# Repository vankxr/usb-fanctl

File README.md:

# USB Fan Controller
There are many USB fan controllers on sale, but none of them allow you to PWM 2-pin fans, as far as I am aware. This controller implements a compatible and widely supported USB serial port interface and allows you to control fans with it. It also supports 1-Wire sensors for temperature measurement.

## Authors

* **João Silva** - [vankxr](https://github.com/vankxr)

## License

The content of this repository is licensed under the [GNU General Public License v3.0](LICENSE).

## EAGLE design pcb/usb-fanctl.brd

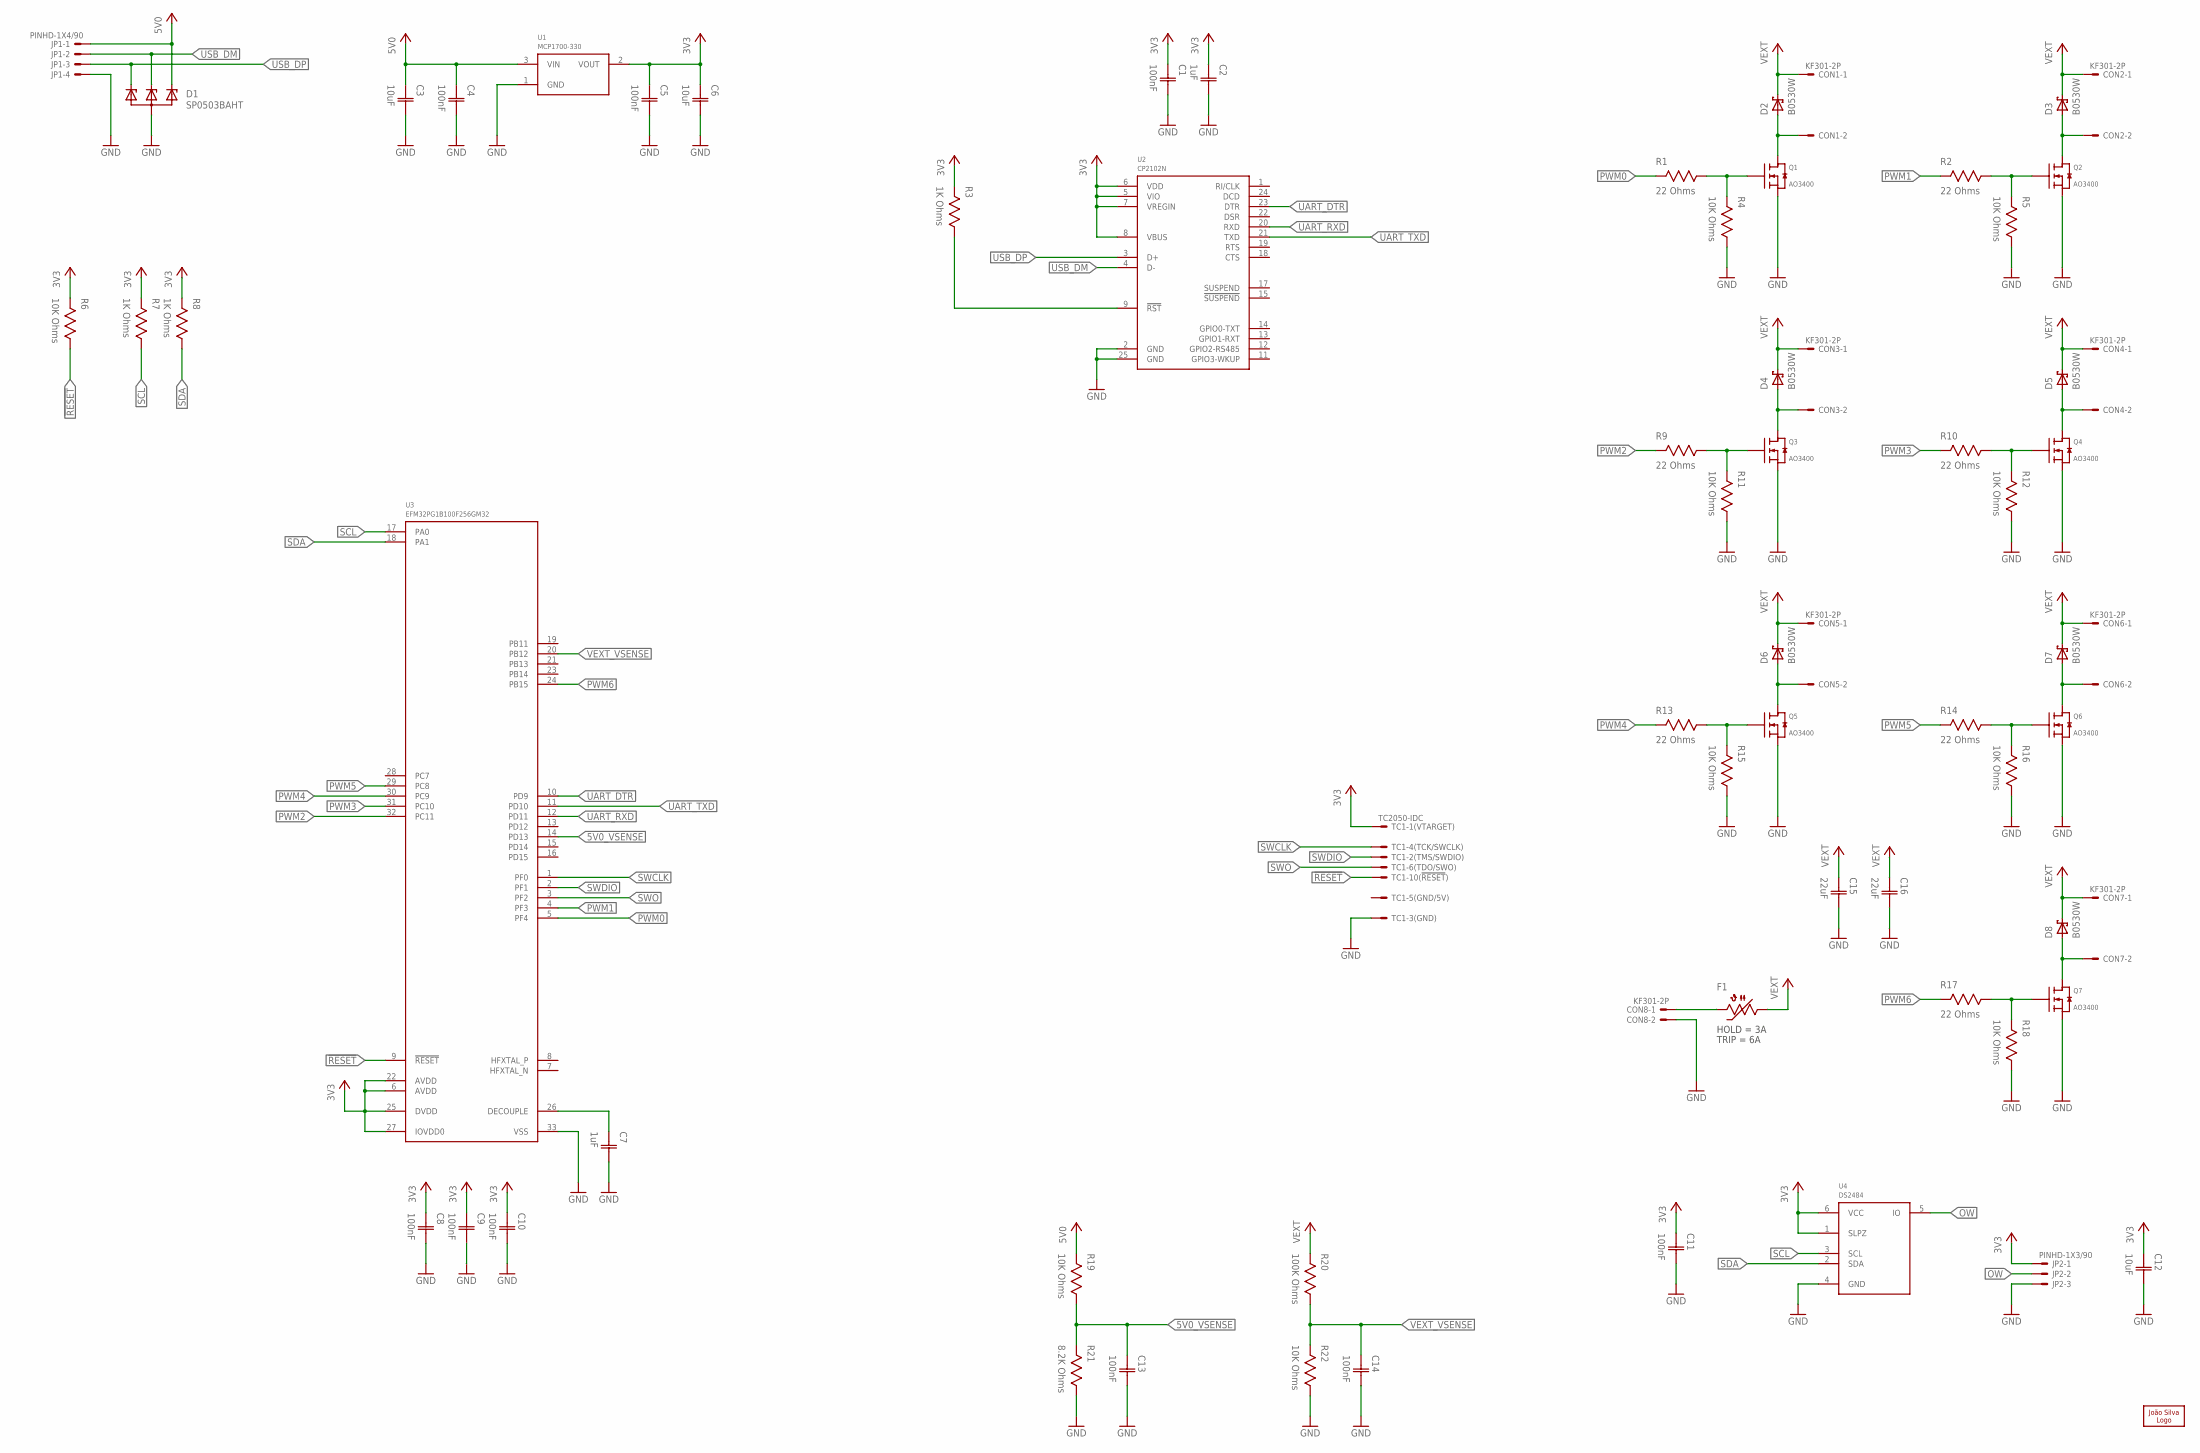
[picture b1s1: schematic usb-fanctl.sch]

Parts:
C1, C4, C5, C8, C9, C10, C11, C13, C14: 100nF; CAP0402
C2, C7: 1uF; CAP0402
C3, C6, C12: 10uF; CAP0603
C15, C16: 22uF; CAP1206
CON1, CON2, CON3, CON4, CON5, CON6, CON7, CON8: KF301-2P
D1: SP0503BAHT; SOT143
D2, D3, D4, D5, D6, D7, D8: B0530W; SOD-123
F1: PTC1206; 1206
JP1: PINHD-1X4/90; 1X04/90
JP2: PINHD-1X3/90; 1X03/90
LOGO1: JS-5MM; JS_5MM
Q1, Q2, Q3, Q4, Q5, Q6, Q7: AO3400; SOT23
R1, R2, R9, R10, R13, R14, R17: 22 Ohms; RES0402
R3, R7, R8: 1K Ohms; RES0402
R4, R5, R6, R11, R12, R15, R16, R18, R19, R22: 10K Ohms; RES0402
R20: 100K Ohms; RES0402
R21: 8.2K Ohms; RES0402
TC1: TC2050-IDC
U1: MCP1700-330; SOT23
U2: CP2102N; QFN24
U3: EFM32PG1B100F256GM32; QFN32_0.5P_JPG
U4: DS2484; SOT23-6

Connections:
3V3: C1.1 (C1), C2.1 (C1), C5.1 (C1), C6.1 (C1), C8.1 (C1), C9.1 (C1), C10.1 (C1), C11.1 (C1), C12.1 (C1), JP2.1, R3.2, R6.2, R7.2, R8.2, TC1.1, U1.2 (VOUT), U2.5 (VIO), U2.6 (VDD), U2.7 (VREGIN), U2.8 (VBUS), U3.6 (AVDD), U3.22 (AVDD), U3.25 (DVDD), U3.27 (IOVDD0), U4.1 (SLPZ), U4.6 (VCC)
5V0: C3.1 (C1), C4.1 (C1), D1.4 (C3), JP1.1, R19.2, U1.3 (VIN)
5V0_VSENSE: C13.1 (C1), R19.1, R21.2, U3.14 (PD13)
!RESET: R6.1, TC1.10, U3.9 (!RESET)
GND: C1.2 (C2), C2.2 (C2), C3.2 (C2), C4.2 (C2), C5.2 (C2), C6.2 (C2), C7.2 (C2), C8.2 (C2), C9.2 (C2), C10.2 (C2), C11.2 (C2), C12.2 (C2), C13.2 (C2), C14.2 (C2), C15.2 (C2), C16.2 (C2), CON8.2, D1.1 (A), JP1.4, JP2.3, Q1.2 (S), Q2.2 (S), Q3.2 (S), Q4.2 (S), Q5.2 (S), Q6.2 (S), Q7.2 (S), R4.1, R5.1, R11.1, R12.1, R15.1, R16.1, R18.1, R21.1, R22.1, TC1.3, U1.1 (GND), U2.2 (GND), U2.25 (GND), U3.33 (VSS), U4.4 (GND)
unnamed: Q2.1 (G), R2.1, R5.2
unnamed: CON2.2, D3.A, Q2.3 (D)
unnamed: Q4.1 (G), R10.1, R12.2
unnamed: CON4.2, D5.A, Q4.3 (D)
unnamed: Q6.1 (G), R14.1, R16.2
unnamed: CON6.2, D7.A, Q6.3 (D)
unnamed: Q7.1 (G), R17.1, R18.2
unnamed: CON7.2, D8.A, Q7.3 (D)
unnamed: Q1.1 (G), R1.1, R4.2
unnamed: CON1.2, D2.A, Q1.3 (D)
unnamed: Q3.1 (G), R9.1, R11.2
unnamed: CON3.2, D4.A, Q3.3 (D)
unnamed: Q5.1 (G), R13.1, R15.2
unnamed: CON5.2, D6.A, Q5.3 (D)
unnamed: C7.1 (C1), U3.26 (DECOUPLE)
unnamed: R3.1, U2.9 (!RST)
OW: JP2.2, U4.5 (IO)
PWM0: R1.2, U3.5 (PF4)
PWM1: R2.2, U3.4 (PF3)
PWM2: R9.2, U3.32 (PC11)
PWM3: R10.2, U3.31 (PC10)
PWM4: R13.2, U3.30 (PC9)
PWM5: R14.2, U3.29 (PC8)
PWM6: R17.2, U3.24 (PB15)
SCL: R7.1, U3.17 (PA0), U4.3 (SCL)
SDA: R8.1, U3.18 (PA1), U4.2 (SDA)
SWCLK: TC1.4, U3.1 (PF0)
SWDIO: TC1.2, U3.2 (PF1)
SWO: TC1.6, U3.3 (PF2)
UART_DTR: U2.23 (DTR), U3.10 (PD9)
UART_RXD: U2.20 (RXD), U3.12 (PD11)
UART_TXD: U2.21 (TXD), U3.11 (PD10)
USB_DM: D1.3 (C2), JP1.2, U2.4 (D-)
USB_DP: D1.2 (C1), JP1.3, U2.3 (D+)
VEXT: C15.1 (C1), C16.1 (C1), CON1.1, CON2.1, CON3.1, CON4.1, CON5.1, CON6.1, CON7.1, D2.C, D3.C, D4.C, D5.C, D6.C, D7.C, D8.C, F1.1, R20.2
VEXT_UNFUSED: CON8.1, F1.2
VEXT_VSENSE: C14.1 (C1), R20.1, R22.2, U3.20 (PB12)

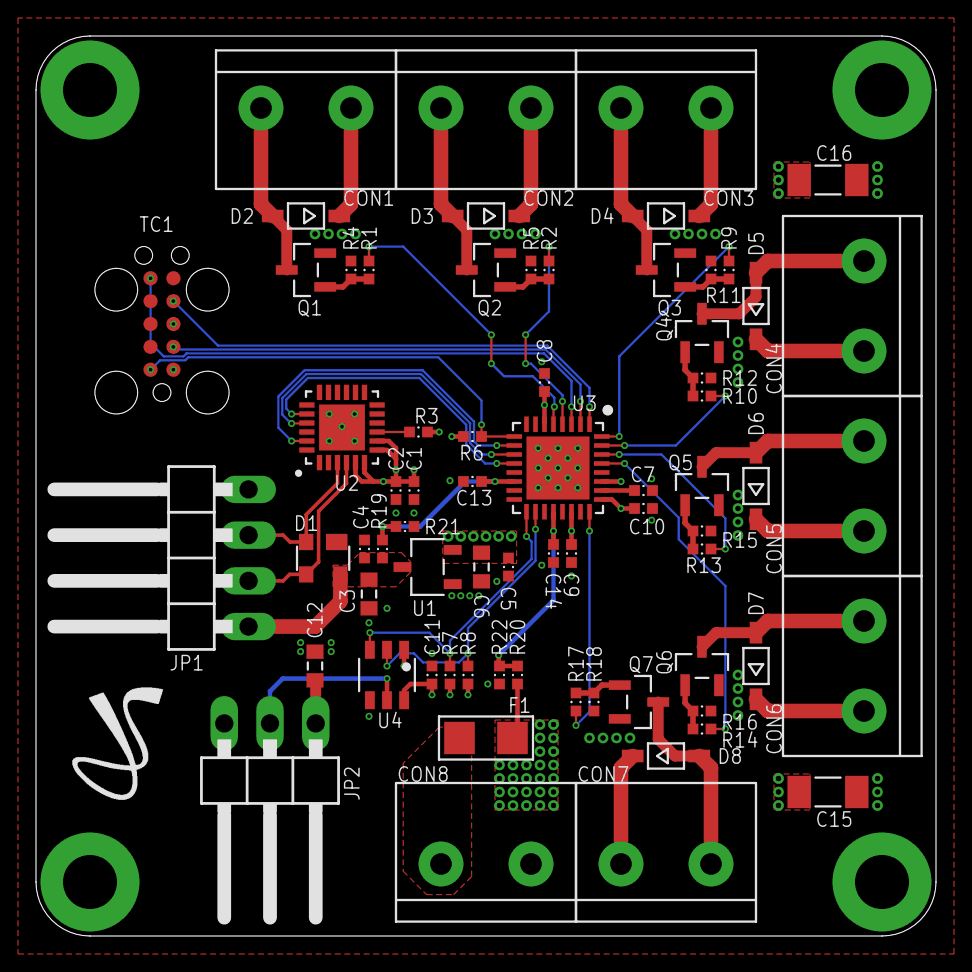
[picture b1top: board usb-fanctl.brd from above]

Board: 4 copper layers, 50.0 x 50.0 mm, 70 parts (0 on the bottom side), 42 nets.

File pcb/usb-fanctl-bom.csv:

Comment,Footprint,Designator
PTC 3A,PTC1206,F1
100K Ohms,RES0402,R20
100nF,CAP0402,"C1, C4, C5, C8, C9, C10, C11, C13, C14"
10K Ohms,RES0402,"R4, R5, R6, R11, R12, R15, R16, R18, R19, R22"
10uF,CAP0603,"C3, C6, C12"
1K Ohms,RES0402,"R3, R7, R8"
1uF,CAP0402,"C2, C7"
22 Ohms,RES0402,"R1, R2, R9, R10, R13, R14, R17"
22uF,CAP1206,"C15, C16"
8.2K Ohms,RES0402,R21
AO3400,SOT23,"Q1, Q2, Q3, Q4, Q5, Q6, Q7"
B0530W,SOD-123,"D2, D3, D4, D5, D6, D7, D8"
CP2102N,QFN24,U2
DS2484,SOT23-6,U4
EFM32PG1B100F256GM32,QFN32_0.5P_JPG,U3
KF301-2P,KF301-2P,"CON1, CON2, CON3, CON4, CON5, CON6, CON7, CON8"
MCP1700-330,SOT23,U1
PINHD-1X3/90,1X03/90,JP2
PINHD-1X4/90,1X04/90,JP1
SP0503BAHT,SOT143,D1

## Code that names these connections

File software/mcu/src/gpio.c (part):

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                      | GPIO_P_MODEH_MODE9_DISABLED         // NC
                      | GPIO_P_MODEH_MODE10_DISABLED        // NC
                      | GPIO_P_MODEH_MODE11_DISABLED        // NU
                      | GPIO_P_MODEH_MODE12_DISABLED        // VEXT_VSENSE
                      | GPIO_P_MODEH_MODE13_DISABLED        // NU
                      | GPIO_P_MODEH_MODE14_DISABLED        // NU
                      | GPIO_P_MODEH_MODE15_PUSHPULL;       // PWM6 - TIM1_CC3 Location 7
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                      | GPIO_P_MODEL_MODE6_DISABLED             // NC
                      | GPIO_P_MODEL_MODE7_DISABLED;            // NC
    GPIO->P[3].MODEH  = GPIO_P_MODEH_MODE8_DISABLED             // NC
                      | GPIO_P_MODEH_MODE9_INPUTPULL            // UART_DTR
                      | GPIO_P_MODEH_MODE10_INPUTPULL           // UART_TXD - US0_RX Location 17
                      | GPIO_P_MODEH_MODE11_PUSHPULL            // UART_RXD - US0_TX Location 19
                      | GPIO_P_MODEH_MODE12_DISABLED            // NU
                      | GPIO_P_MODEH_MODE13_DISABLED            // 5V0_VSENSE
                      | GPIO_P_MODEH_MODE14_DISABLED            // NU
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
    // Debugger Route
    GPIO->ROUTEPEN &= ~(GPIO_ROUTEPEN_TDIPEN | GPIO_ROUTEPEN_TDOPEN); // Disable JTAG
    GPIO->ROUTEPEN |= GPIO_ROUTEPEN_SWVPEN; // Enable SWO
    GPIO->ROUTELOC0 = GPIO_ROUTELOC0_SWVLOC_LOC0; // SWO on PF2

    // External interrupts
    GPIO->EXTIPSELL = GPIO_EXTIPSELL_EXTIPSEL0_PORTA            // NU
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
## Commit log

2021-11-01 Add PCB files
2021-11-01 Add production files
2021-11-02 Fix schematic sheet attributes not showing
2021-12-29 Add MCU software
2021-12-29 Add CLI tool software
2022-01-24 Add .deb packaging folder
2022-06-20 Add frequency setting Rename CLI app
